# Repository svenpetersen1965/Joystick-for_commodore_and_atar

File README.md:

# Joystick-for_commodore_and_atar
This is a joystick for Commodore C64 etc.

The Design is based on the widely available ZIPPYY joystick, which is of a  great quality.

There are now three alternative top shells:

The original ZIPPYY top has a mounting hole distance of 52mm (square), the "HK-T-8YT" a distance of 32mm and the "50sq-28" a distance of 50mm (a ZIPPYY clone). The light blue lines show, how the distances were measured. 

Find some info on the required cable making <a href="http://tech.guitarsite.de/cable_making.html">on my website</a>

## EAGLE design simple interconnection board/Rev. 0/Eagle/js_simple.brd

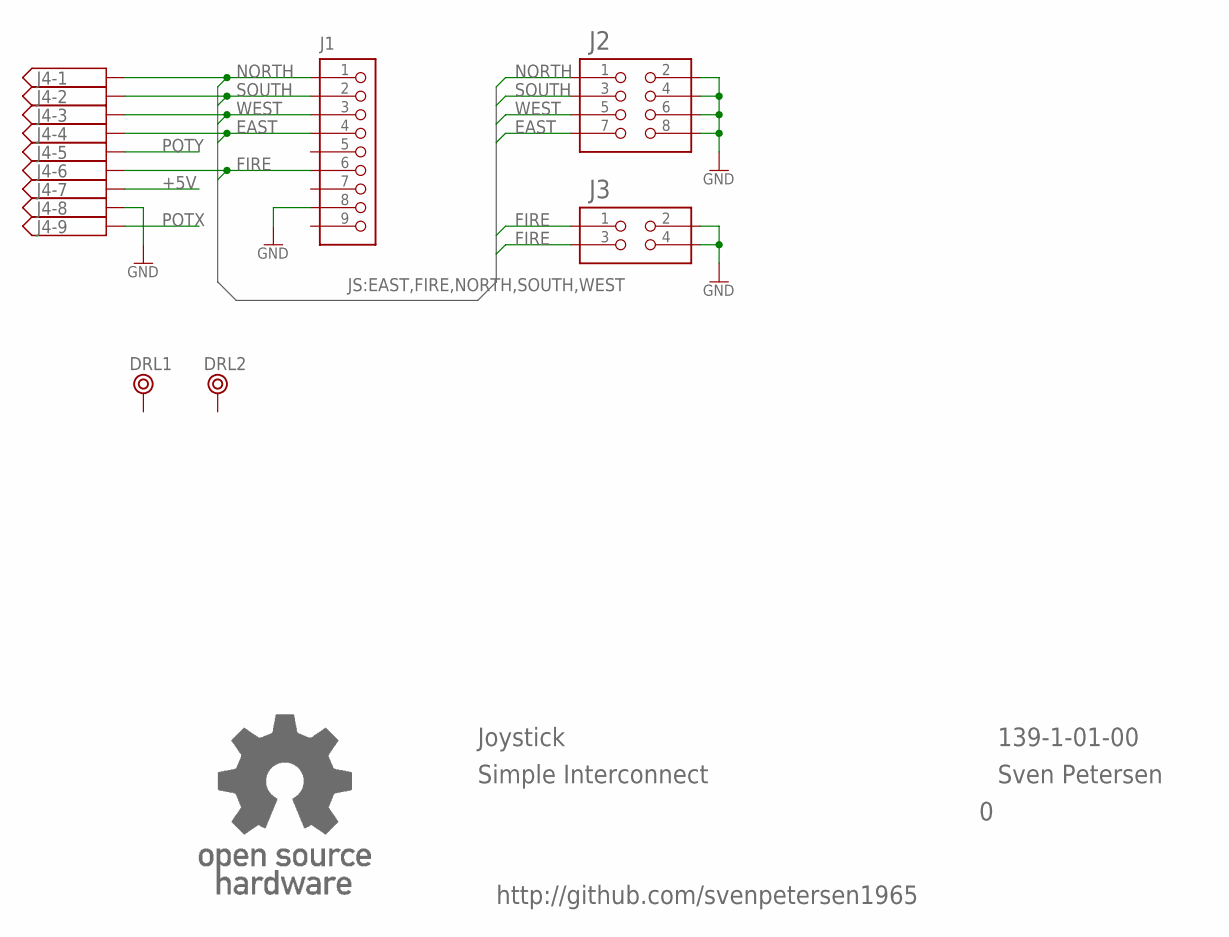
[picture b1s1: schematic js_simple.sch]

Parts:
DRL1, DRL2: BOHR3,5
J1: PINHD-1X9; 1X09
J2: PINHD-2X4; 2X04
J3: PINHD-2X2; 2X02
J4: 9X1X2SMD; 9PIN_1X2SMD
U$8: OPEN_SOURCE_HW; OPENHW

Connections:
+5V: J4.7
EAST: J1.4, J2.7, J4.4
FIRE: J1.6, J3.1, J3.3, J4.6
GND: J1.8, J2.2, J2.4, J2.6, J2.8, J3.2, J3.4, J4.8
NORTH: J1.1, J2.1, J4.1
POTX: J4.9
POTY: J4.5
SOUTH: J1.2, J2.3, J4.2
WEST: J1.3, J2.5, J4.3

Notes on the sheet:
Joystick
Simple Interconnect
139-1-01-00
Sven Petersen
http://github.com/svenpetersen1965

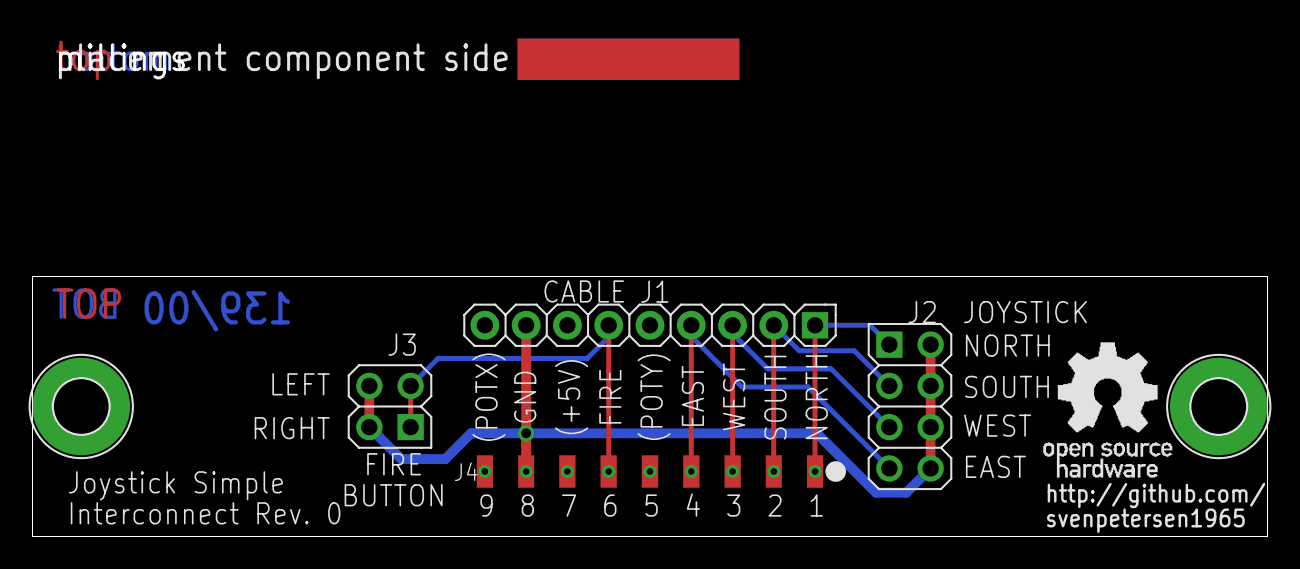
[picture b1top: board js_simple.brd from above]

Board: 2 copper layers, 76.0 x 31.0 mm, 9 parts (0 on the bottom side), 6 nets.

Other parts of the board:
U$6: PCB-TITLE/
U$7: 2LAYER

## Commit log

2020-01-22 Initial upload
2020-02-19 Two new top shells for different joystick types
2020-02-19 Delete Joystick v15.f3d
    Obsolete
2020-08-11 Silk Screen Update
